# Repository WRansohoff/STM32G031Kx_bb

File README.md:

# Simple STM32G031Kx Breakout Board

This is just a simple reference circuit for a 32-pin STM32G031 microcontroller. I tried to make it easy to hand-solder, with everything on one side of the board, wide footprints, and no parts smaller than 0805. The microcontroller also has pins spaced at 0.8mm, which is farther apart than the usual <=0.5mm that you see these days. Some of the parts are a little close together, so you might have to think about the order that you solder them on if you don't reflow it. But it should be do-able without much soldering experience required.

Note: Embarrassingly, I forgot to connect the +3.3V line to the microcontroller's `VDD` pin on the first revision, so the boards only worked after I soldered a wire between those two nets. That should be fixed now, but I can't guarantee that until I've ordered and tested the new revision. I'm also thinking of replacing the through-hole crystal with a surface-mount one, so the BoM might still change slightly.

Sorry for the inconvenience, in the meantime!

# Board Renders:

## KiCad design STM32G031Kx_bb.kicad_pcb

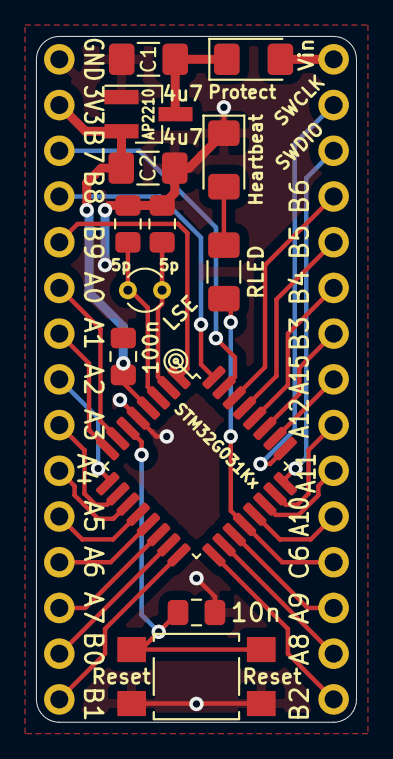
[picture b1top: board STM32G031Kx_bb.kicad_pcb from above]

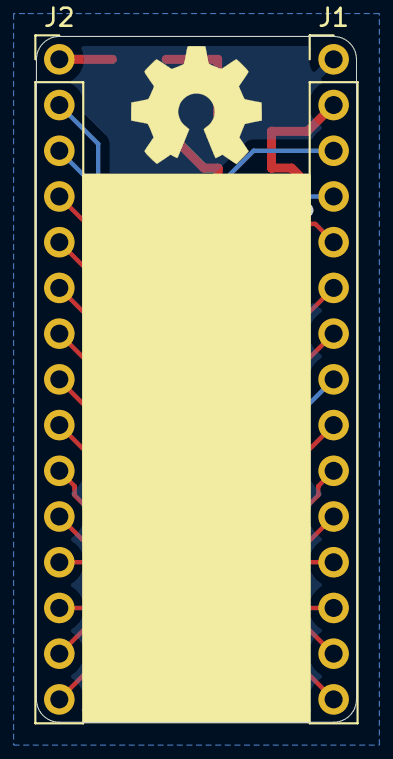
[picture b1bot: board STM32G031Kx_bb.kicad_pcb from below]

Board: 2 copper layers, 17.8 x 38.1 mm, 15 parts (2 on the bottom side), 35 nets.

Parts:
C1, C2: 4u7; C_1206_3216Metric_Pad1.42x1.75mm_HandSolder
C3, C4: 5p; C_0805_2012Metric_Pad1.15x1.40mm_HandSolder
C5: 100n; C_0805_2012Metric_Pad1.15x1.40mm_HandSolder
C6: 10n; C_0805_2012Metric_Pad1.15x1.40mm_HandSolder
D1: Protect; D_1206_3216Metric_Pad1.42x1.75mm_HandSolder
D2: Heartbeat; LED_1206_3216Metric_Pad1.42x1.75mm_HandSolder
J1: GPIO1; PinHeader_1x15_P2.54mm_Vertical
J2: GPIO2; PinHeader_1x15_P2.54mm_Vertical
R1: RLED; R_1206_3216Metric_Pad1.42x1.75mm_HandSolder
SW1: Reset; SW_SPST_TL3305A
U1: STM32G031Kx; LQFP-32_7x7mm_P0.8mm
U2: AP2210; SOT-23_Handsoldering
Y1: LSE; Crystal_Round_D2.0mm_Vertical

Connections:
A0: J1.6, U1.7
A1: J1.7, U1.8
A2: J1.8, U1.9
A3: J1.9, U1.10
A4: J1.10, U1.11
A5: J1.11, U1.12
A6: J1.12, U1.13
A7: J1.13, U1.14
A8: J2.14, U1.18
A9: J2.13, U1.19
A10: J2.11, U1.21
A11: J2.10, U1.22
A12: J2.9, U1.23
A15: J2.8, U1.26
B0: J1.14, U1.15
B1: J1.15, U1.16
B2: J2.15, U1.17
B3: J2.7, U1.27
B4: J2.6, U1.28
B5: J2.5, U1.29
B6: J2.4, U1.30
B7: J1.3, U1.31
B8: J1.4, U1.32
B9: J1.5, U1.1
C6: J2.12, R1.1, U1.20
GND: C1.2, C2.2, C3.2, C4.1, C5.2, C6.2, D2.1, J1.1, SW1.1, U1.5, U2.1
unnamed: C1.1, D1.1, U2.3
unnamed: C3.1, U1.3, Y1.1
unnamed: C4.2, U1.2, Y1.2
unnamed: C6.1, SW1.2, U1.6
unnamed: D2.2, R1.2
SWCLK: J2.2, U1.25
SWDIO: J2.3, U1.24
VDD: C2.1, C5.1, J1.2, U1.4, U2.2
VPP: D1.2, J2.1

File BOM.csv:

Part ID,Part type,Part size,Part value,Example Digikey Item,Cost (qty: 1),Comment
"C1, C2",Capacitor,1206,4.7μF,https://www.digikey.com/short/p2pnd5,$0.50,"Bulk power supply decoupling capacitors. 2.2μF - 10μF is probably fine, prefer X5/X7 ceramic capacitors with low ESR."
"C2, C3",Capacitor,0805,5pF,https://www.digikey.com/short/p2pnrf,$0.20,"Filtering capacitors for the 32.768KHz low-speed crystal oscillator. The actual value depends on your crystal, but it will probably be between 0-15pF and isn't hugely important. Prefer C0G/NP0 ceramic capacitors."
C5,Capacitor,0805,100nF,https://www.digikey.com/short/p2pnw5,$0.10,Decoupling capacitor for the only power pair of supply pins on the QFP32 STM32G031 package. Prefer X5/X7 ceramic capacitors.
C6,Capacitor,0805,10nF,https://www.digikey.com/short/p2pn24,$0.10,"Filtering capacitor for the reset button. This is recommended by ST's application notes. Although, I wonder - should there also be a resistor in series between the reset pin and the button?"
D1,Schottky Diode,1206,"20-40V, 0.5-2A",https://www.digikey.com/short/p2pnv4,$0.40,"Schottky diode to protect against reverse polarity. This will probably introduce a ~0.3-0.6V drop before the voltage regulator, but it should prevent the circuit from frying if you swap + and - by accident."
D2,LED,1206,Your favorite color,https://www.digikey.com/short/p2pdmb,$0.20,"Heartbeat' LED - it's nice for a board to include at least one LED for a program to use. Also, the QFP32 STM32G031 includes a single pin from the GPIOC bank, which is nice for this sort of thing. I think that you aren't supposed to sink more than 20mA from each bank, so using pin C6 to drive an LED doesn't limit what we can do on the GPIOA or GPIOB banks."
"J1, J2",Pin Header or Socket Row,"0.1""",1x15,https://www.digikey.com/short/p2pdvt,$0.74,"These are generic parts, and you can find them much more cheaply on eBay, Amazon, AliExpress, etc. You can usually get good deals on bunches of 1x40 rows, and cut them to size."
R1,Resistor,1206,1KΩ,https://www.digikey.com/short/p2p0ht,$0.10,"If you want to use PWM to drive the LED, maybe 220-470Ω would be better. If you want it to be dim, maybe 4.7KΩ-10KΩ? Red/yellow LEDs will be brighter than green/blue/white LEDs for the same value of resistance, because their forward voltages are lower."
SW1,Button,"0.45""x0.45""",SPST,https://www.digikey.com/short/p2p09q,$0.22,"I picked the 'TL3305A' part because it was reasonably cheap and in the default KiCAD footprint library. But any old 4-leg SMD 0.45""x0.45"" tactile button will probably work."
U1,Microcontroller,LQFP-32,STM32G031Kx,https://www.digikey.com/short/p2p05b,$1.86,"The core MCU. Be sure to double-check where pin #1 goes - look in the datasheet for the 'pin 1' marking location. There are currently two versions available; the one ending in 'K6' is cheaper, but only has 32KB of Flash memory. The one ending in 'K8' has 64KB Flash."
U2,Voltage Regulator,SOT-23,AP2210-3.3,https://www.digikey.com/short/p2p090,$0.42,"I like this voltage regulator because it only has 3 pins, it can supply a decent 300mA, and it works with up to a 13V input. But I'm starting to think it's a good idea to use regulators with 'power good' pins tied to the reset line."
Y1,Crystal,2mm-Diameter,32.768KHz,https://www.digikey.com/short/p2p0b2,$0.21,"Low-Speed External' crystal oscillator. I used a cylindrical 2mm-diameter through-hole crystal because it's a very standard size, but here's an exercise for the reader - replace it with a small SMD crystal!"
Total,-,-,-,-,$5.05,"You can pay a bit less per unit if you buy in 10s or 100s, but then you'd need to make 10 or 100 of these. SMD resistors and capacitors can be worth buying in bulk, though."

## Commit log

2019-09-24 Add MIT license
2019-09-24 Add readme and bill of materials
2019-09-24 Add core project files, and custom parts library.
2019-09-24 Add a couple more files.
2019-09-24 Remove the netlist; it's one button-click away, and I don't think that counts as a 'core file'.
2019-09-24 Add OSHPark renders of the board top/bottom
2019-09-24 Update readme.
2019-09-24 Clean up the silkscreen markings a bit.
2019-10-06 Connect the MCU power supply to the voltage regulator's output...whoops!
2019-10-07 Update Readme to reflect where the design is at.
